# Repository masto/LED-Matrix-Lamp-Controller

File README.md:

# LED Matrix Lamp Controller

A little Arduino-based controller board to go inside one of [these guys](https://community.glowforge.com/t/matrix-lamp/45621).

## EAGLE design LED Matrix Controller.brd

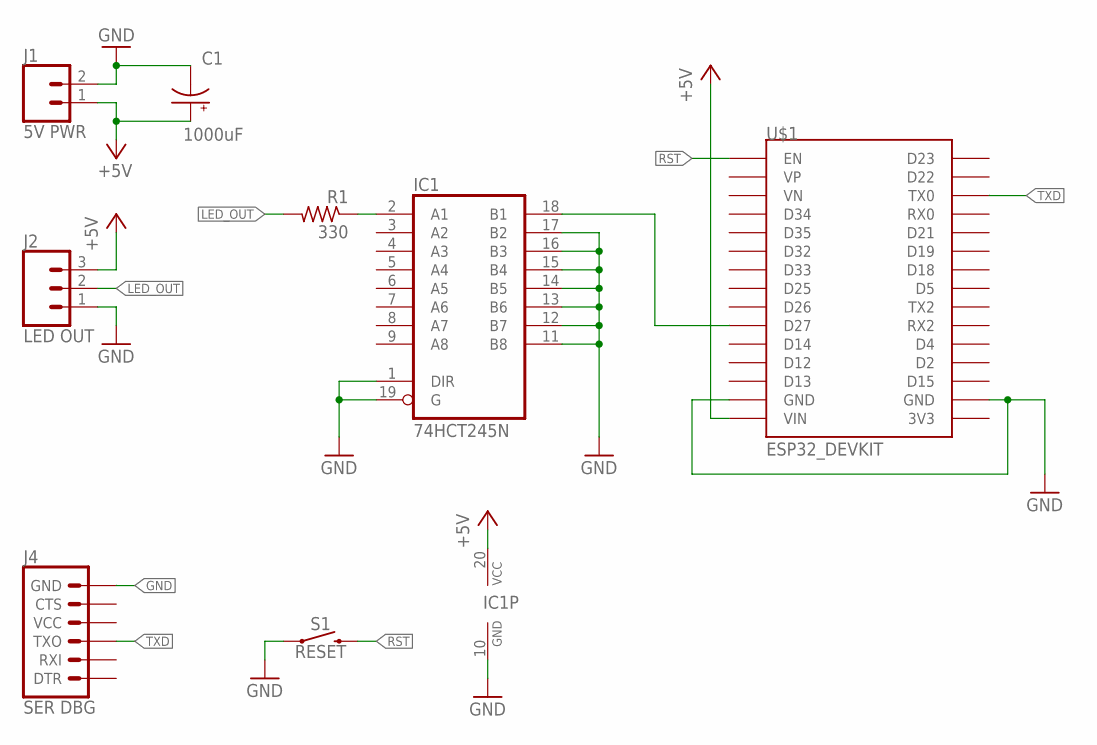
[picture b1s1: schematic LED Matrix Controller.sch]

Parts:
C1: 1000uF; E5-10,5
IC1: 74HCT245N; DIL20
J1: 5V PWR; SCREWTERMINAL-5MM-2
J2: LED OUT; SCREWTERMINAL-5MM-3
J4: SER DBG; 6_PIN_SERIAL_TARGET_SIDE_W_SILK
R1: 330; 0207/10
S1: RESET; TACTILE_SWITCH_PTH_6.0MM
U$1: ESP32_DEVKIT

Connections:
+5V: C1.+, IC1.20 (VCC), J1.1, J2.3, U$1.VIN
GND: C1.-, IC1.1 (DIR), IC1.10 (GND), IC1.11 (B8), IC1.12 (B7), IC1.13 (B6), IC1.14 (B5), IC1.15 (B4), IC1.16 (B3), IC1.17 (B2), IC1.19 (G), J1.2, J2.1, J4.P$6 (GND), S1.1, U$1.GND@1 (GND), U$1.GND@2 (GND)
LED_OUT: J2.2, R1.2
unnamed: IC1.18 (B1), U$1.D27
unnamed: IC1.2 (A1), R1.1
RST: S1.3 (2), U$1.EN
TXD: J4.P$2 (TXO), U$1.TX0

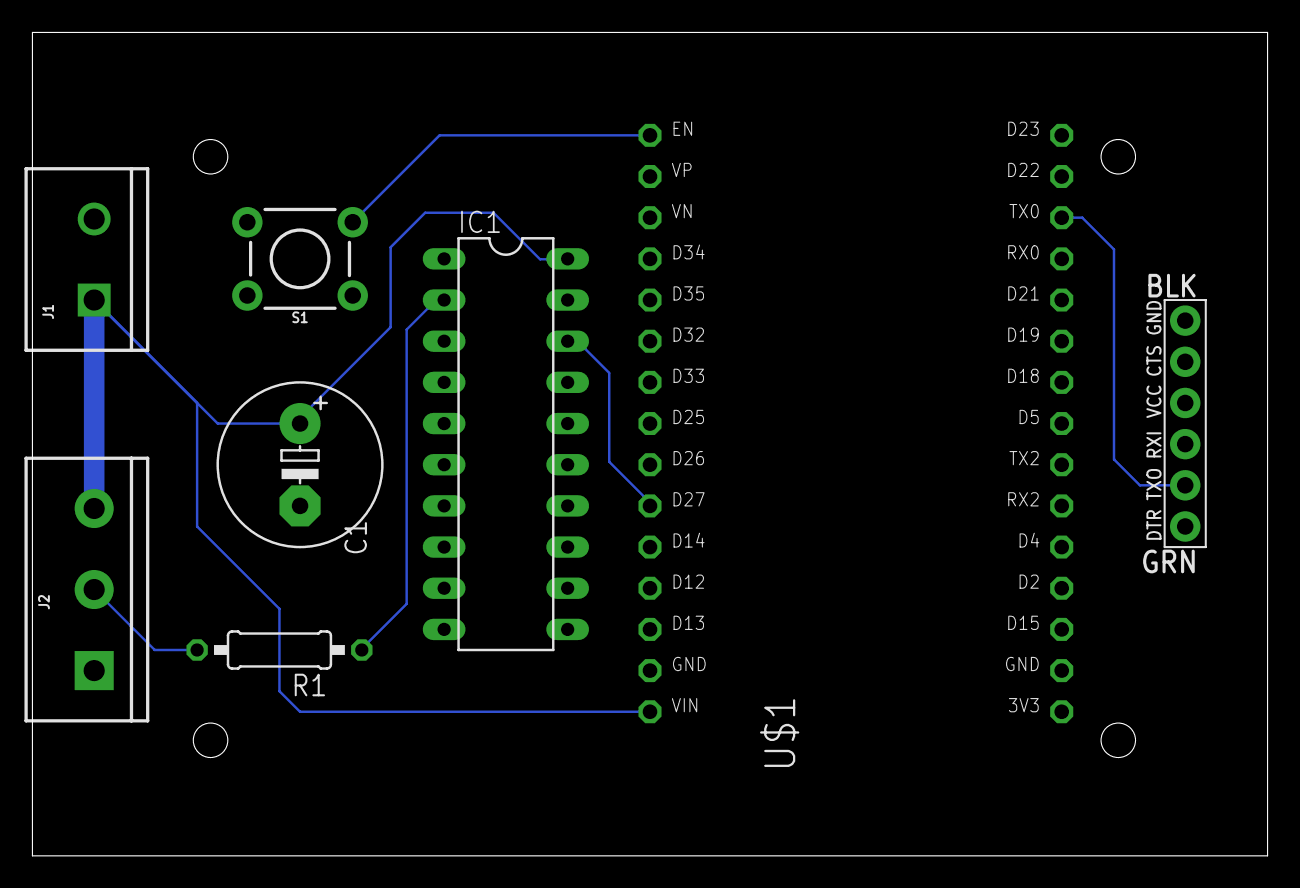
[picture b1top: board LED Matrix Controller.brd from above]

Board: 2 copper layers, 76.2 x 50.8 mm, 8 parts (0 on the bottom side), 7 nets.

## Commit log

2020-01-01 Stash a working of the controller board
    This is super minimalist at the moment, just the ATmega368p, couple of
    passives, and connectors. But it's built and tested, so I don't want
    to lose it as I go on adding stuff.
2020-01-04 Add ISP and serial debug headers
    Somewhat useful for not having to remove the chip to reprogram it.
    ISP header needs a wire to connect 5v. I thought that wasn't needed
    but once I tested it, apparently it is.
2020-01-05 Add a reset button
2020-01-20 Create a two-layer version
    A couple of small updates for manufacturing a 2 layer board. Route
    power to the ICSP header and the rest of the FTDI serial header
    signals since it's easy now.
2020-01-20 Replace ATmega328P with ESP32 dev board
    Quick and dirty routing to stick a DOIT ESP32 dev module on the
    board. No attention given to RF keepout.
2020-01-25 Add a 74HCT245 as a level shifter
    The ESP32 uses 3.3v logic, and even though it "worked" on my test
    board, it's possible that I was just lucky. The Internet wants me to
    use this chip, even though I'm wasting 7 buffers for a single I/O.
    I'd like to build up one of these, but I will probably change it later
    for something smaller.

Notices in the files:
parts and their libraries:
SparkFun-Connectors: Licensing: Creative Commons ShareAlike 4.0 International - https://creativecommons.org/licenses/by-sa/4.0
